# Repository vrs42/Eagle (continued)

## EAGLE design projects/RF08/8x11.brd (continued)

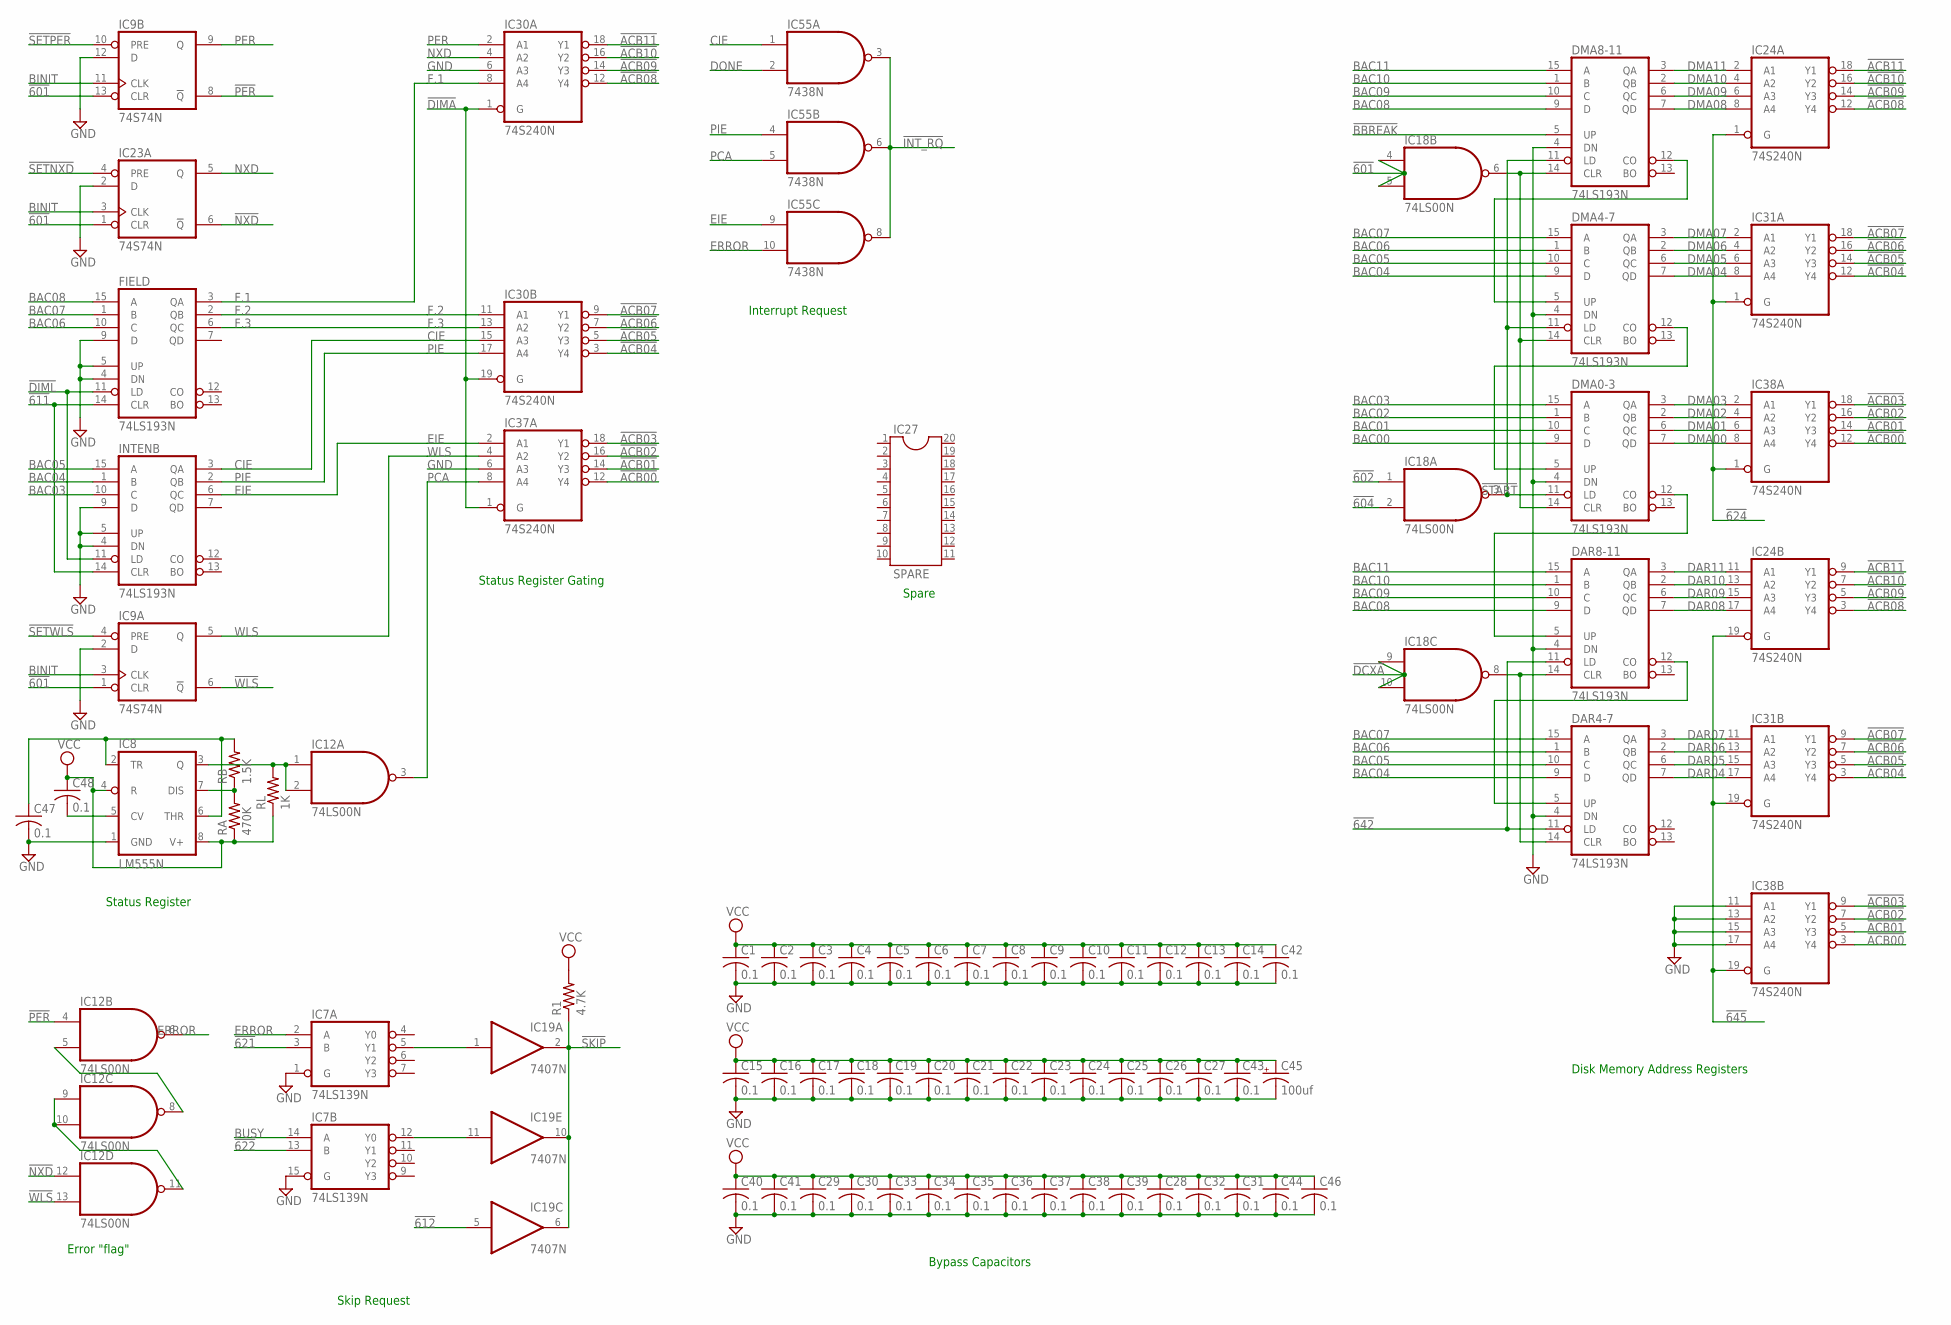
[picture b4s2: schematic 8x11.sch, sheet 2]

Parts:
C1, C2, C3, C4, C5, C6, C7, C8, C9, C10, C11, C12, C13, C14, C15, C16, C17, C18, C19, C20, C21, C22, C23, C24, C25, C26, C27, C28, C29, C30, C31, C32, C33, C34, C35, C36, C37, C38, C39, C40, C41, C42, C43, C44, C46, C47, C48: 0.1; C050-025X075
C45: 100uf; E22-6
DAR4-7, DAR8-11: 74LS193N; DIL16
DMA0-3, DMA4-7, DMA8-11: 74LS193N; DIL16
FIELD: 74LS193N; DIL16
IC7: 74LS139N; DIL16
IC8: LM555N; DIL08
IC9, IC23: 74S74N; DIL14
IC12, IC18: 74LS00N; DIL14
IC19: 7407N; DIL14
IC24, IC30, IC31, IC37, IC38: 74S240N; DIL20
IC27: SPARE; DIL20
IC55: 7438N; DIL14
INTENB: 74LS193N; DIL16
R1: 4.7K; 0207/10
RA: 470K; 0207/10
RB: 1.5K; 0207/10
RL: 1K; 0207/10

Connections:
!601: IC9.1 (CLR), IC9.13 (CLR), IC18.4 (I0), IC18.5 (I1), IC23.1 (CLR); also elsewhere on the board
!602: IC18.1 (I0); also elsewhere on the board
!604: IC18.2 (I1); also elsewhere on the board
!611: FIELD.14 (CLR), INTENB.14 (CLR); also elsewhere on the board
!612: IC19.5 (I); also elsewhere on the board
!621: IC7.3 (B); also elsewhere on the board
!622: IC7.13 (B); also elsewhere on the board
!624: IC24.1 (G), IC31.1 (G), IC38.1 (G); also elsewhere on the board
!642: DAR4-7.11 (LD), DAR8-11.11 (LD); also elsewhere on the board
!645: IC24.19 (G), IC31.19 (G), IC38.19 (G); also elsewhere on the board
!ACB00: IC37.12 (Y4), IC38.3 (Y4), IC38.12 (Y4); also elsewhere on the board
!ACB01: IC37.14 (Y3), IC38.5 (Y3), IC38.14 (Y3); also elsewhere on the board
!ACB02: IC37.16 (Y2), IC38.7 (Y2), IC38.16 (Y2); also elsewhere on the board
!ACB03: IC37.18 (Y1), IC38.9 (Y1), IC38.18 (Y1); also elsewhere on the board
!ACB04: IC30.3 (Y4), IC31.3 (Y4), IC31.12 (Y4); also elsewhere on the board
!ACB05: IC30.5 (Y3), IC31.5 (Y3), IC31.14 (Y3); also elsewhere on the board
!ACB06: IC30.7 (Y2), IC31.7 (Y2), IC31.16 (Y2); also elsewhere on the board
!ACB07: IC30.9 (Y1), IC31.9 (Y1), IC31.18 (Y1); also elsewhere on the board
!ACB08: IC24.3 (Y4), IC24.12 (Y4), IC30.12 (Y4); also elsewhere on the board
!ACB09: IC24.5 (Y3), IC24.14 (Y3), IC30.14 (Y3); also elsewhere on the board
!ACB10: IC24.7 (Y2), IC24.16 (Y2), IC30.16 (Y2); also elsewhere on the board
!ACB11: IC24.9 (Y1), IC24.18 (Y1), IC30.18 (Y1); also elsewhere on the board
!BBREAK: DMA8-11.5 (UP); also elsewhere on the board
!DCXA: IC18.9 (I0), IC18.10 (I1); also elsewhere on the board
!DIMA: IC30.1 (G), IC30.19 (G), IC37.1 (G); also elsewhere on the board
!DIML: FIELD.11 (LD), INTENB.11 (LD); also elsewhere on the board
!INT_RQ: IC55.3 (O), IC55.6 (O), IC55.8 (O); also elsewhere on the board
!NXD: IC12.12 (I0), IC23.6 (!Q)
!PER: IC9.8 (!Q), IC12.4 (I0)
!SETNXD: IC23.4 (PRE); also elsewhere on the board
!SETPER: IC9.10 (PRE); also elsewhere on the board
!SETWLS: IC9.4 (PRE); also elsewhere on the board
!SKIP: IC19.2 (O), IC19.6 (O), IC19.10 (O), R1.1; also elsewhere on the board
!START: DMA0-3.11 (LD), DMA4-7.11 (LD), DMA8-11.11 (LD), IC18.3 (O)
!WLS: IC9.6 (!Q), IC12.13 (I1)
BAC00: DMA0-3.9 (D); also elsewhere on the board
BAC01: DMA0-3.10 (C); also elsewhere on the board
BAC02: DMA0-3.1 (B); also elsewhere on the board
BAC03: DMA0-3.15 (A), INTENB.10 (C); also elsewhere on the board
BAC04: DAR4-7.9 (D), DMA4-7.9 (D), INTENB.1 (B); also elsewhere on the board
BAC05: DAR4-7.10 (C), DMA4-7.10 (C), INTENB.15 (A); also elsewhere on the board
BAC06: DAR4-7.1 (B), DMA4-7.1 (B), FIELD.10 (C); also elsewhere on the board
BAC07: DAR4-7.15 (A), DMA4-7.15 (A), FIELD.1 (B); also elsewhere on the board
BAC08: DAR8-11.9 (D), DMA8-11.9 (D), FIELD.15 (A); also elsewhere on the board
BAC09: DAR8-11.10 (C), DMA8-11.10 (C); also elsewhere on the board
BAC10: DAR8-11.1 (B), DMA8-11.1 (B); also elsewhere on the board
BAC11: DAR8-11.15 (A), DMA8-11.15 (A); also elsewhere on the board
BINIT: IC9.3 (CLK), IC9.11 (CLK), IC23.3 (CLK); also elsewhere on the board
BUSY: IC7.14 (A); also elsewhere on the board
CIE: IC30.15 (A3), IC55.1 (I0), INTENB.3 (QA); also elsewhere on the board
DAR04: DAR4-7.7 (QD), IC31.17 (A4); also elsewhere on the board
DAR05: DAR4-7.6 (QC), IC31.15 (A3); also elsewhere on the board
DAR06: DAR4-7.2 (QB), IC31.13 (A2); also elsewhere on the board
DAR07: DAR4-7.3 (QA), IC31.11 (A1); also elsewhere on the board
DAR08: DAR8-11.7 (QD), IC24.17 (A4); also elsewhere on the board
DAR09: DAR8-11.6 (QC), IC24.15 (A3); also elsewhere on the board
DAR10: DAR8-11.2 (QB), IC24.13 (A2); also elsewhere on the board
DAR11: DAR8-11.3 (QA), IC24.11 (A1); also elsewhere on the board
DMA00: DMA0-3.7 (QD), IC38.8 (A4); also elsewhere on the board
DMA01: DMA0-3.6 (QC), IC38.6 (A3); also elsewhere on the board
DMA02: DMA0-3.2 (QB), IC38.4 (A2); also elsewhere on the board
DMA03: DMA0-3.3 (QA), IC38.2 (A1); also elsewhere on the board
DMA04: DMA4-7.7 (QD), IC31.8 (A4); also elsewhere on the board
DMA05: DMA4-7.6 (QC), IC31.6 (A3); also elsewhere on the board
DMA06: DMA4-7.2 (QB), IC31.4 (A2); also elsewhere on the board
DMA07: DMA4-7.3 (QA), IC31.2 (A1); also elsewhere on the board
DMA08: DMA8-11.7 (QD), IC24.8 (A4); also elsewhere on the board
DMA09: DMA8-11.6 (QC), IC24.6 (A3); also elsewhere on the board
DMA10: DMA8-11.2 (QB), IC24.4 (A2); also elsewhere on the board
DMA11: DMA8-11.3 (QA), IC24.2 (A1); also elsewhere on the board
DONE: IC55.2 (I1); also elsewhere on the board
EIE: IC37.2 (A1), IC55.9 (I0), INTENB.6 (QC); also elsewhere on the board
ERROR: IC7.2 (A), IC12.6 (O), IC55.10 (I1)
F.1: FIELD.3 (QA), IC30.8 (A4); also elsewhere on the board
F.2: FIELD.2 (QB), IC30.11 (A1); also elsewhere on the board
F.3: FIELD.6 (QC), IC30.13 (A2); also elsewhere on the board
GND: C1.2, C2.2, C3.2, C4.2, C5.2, C6.2, C7.2, C8.2, C9.2, C10.2, C11.2, C12.2, C13.2, C14.2, C15.2, C16.2, C17.2, C18.2, C19.2, C20.2, C21.2, C22.2, C23.2, C24.2, C25.2, C26.2, C27.2, C28.2, C29.2, C30.2, C31.2, C32.2, C33.2, C34.2, C35.2, C36.2, C37.2, C38.2, C39.2, C40.2, C41.2, C42.2, C43.2, C44.2, C45.-, C46.2, C47.2, DAR4-7.4 (DN), DAR4-7.8 (GND), DAR8-11.4 (DN), DAR8-11.8 (GND), DMA0-3.4 (DN), DMA0-3.8 (GND), DMA4-7.4 (DN), DMA4-7.8 (GND), DMA8-11.4 (DN), DMA8-11.8 (GND), FIELD.4 (DN), FIELD.5 (UP), FIELD.8 (GND), FIELD.9 (D), IC7.1 (G), IC7.8 (GND), IC7.15 (G), IC8.1 (GND), IC9.2 (D), IC9.7 (GND), IC9.12 (D), IC12.7 (GND), IC18.7 (GND), IC19.7 (GND), IC23.2 (D), IC23.7 (GND), IC24.10 (GND), IC30.6 (A3), IC30.10 (GND), IC31.10 (GND), IC37.6 (A3), IC37.10 (GND), IC38.10 (GND), IC38.11 (A1), IC38.13 (A2), IC38.15 (A3), IC38.17 (A4), IC55.7 (GND), INTENB.4 (DN), INTENB.5 (UP), INTENB.8 (GND), INTENB.9 (D); also elsewhere on the board
unnamed: DMA0-3.5 (UP), DMA4-7.12 (CO)
unnamed: DAR4-7.14 (CLR), DAR8-11.14 (CLR), IC18.8 (O)
unnamed: DMA4-7.5 (UP), DMA8-11.12 (CO)
unnamed: DAR8-11.5 (UP), DMA0-3.12 (CO)
unnamed: DMA0-3.14 (CLR), DMA4-7.14 (CLR), DMA8-11.14 (CLR), IC18.6 (O)
unnamed: DAR4-7.5 (UP), DAR8-11.12 (CO)
unnamed: IC7.5 (Y1), IC19.1 (I)
unnamed: IC8.7 (DIS), RA.2, RB.1
unnamed: IC8.3 (Q), IC12.1 (I0), IC12.2 (I1), RL.2
unnamed: C47.1, IC8.2 (TR), IC8.6 (THR), RB.2
unnamed: IC7.12 (Y0), IC19.11 (I)
unnamed: C48.2, IC8.5 (CV)
unnamed: IC12.9 (I0), IC12.10 (I1), IC12.11 (O)
unnamed: IC12.5 (I1), IC12.8 (O)
NXD: IC23.5 (Q), IC30.4 (A2); also elsewhere on the board
PCA: IC12.3 (O), IC37.8 (A4), IC55.5 (I1)
PER: IC9.9 (Q), IC30.2 (A1); also elsewhere on the board
PIE: IC30.17 (A4), IC55.4 (I0), INTENB.2 (QB); also elsewhere on the board
VCC: C1.1, C2.1, C3.1, C4.1, C5.1, C6.1, C7.1, C8.1, C9.1, C10.1, C11.1, C12.1, C13.1, C14.1, C15.1, C16.1, C17.1, C18.1, C19.1, C20.1, C21.1, C22.1, C23.1, C24.1, C25.1, C26.1, C27.1, C28.1, C29.1, C30.1, C31.1, C32.1, C33.1, C34.1, C35.1, C36.1, C37.1, C38.1, C39.1, C40.1, C41.1, C42.1, C43.1, C44.1, C45.+, C46.1, C48.1, DAR4-7.16 (VCC), DAR8-11.16 (VCC), DMA0-3.16 (VCC), DMA4-7.16 (VCC), DMA8-11.16 (VCC), FIELD.16 (VCC), IC7.16 (VCC), IC8.4 (R), IC8.8 (V+), IC9.14 (VCC), IC12.14 (VCC), IC18.14 (VCC), IC19.14 (VCC), IC23.14 (VCC), IC24.20 (VCC), IC30.20 (VCC), IC31.20 (VCC), IC37.20 (VCC), IC38.20 (VCC), IC55.14 (VCC), INTENB.16 (VCC), R1.2, RA.1, RL.1; also elsewhere on the board
WLS: IC9.5 (Q), IC37.4 (A2); also elsewhere on the board

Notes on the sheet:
Disk Memory Address Registers
Status Register
Status Register Gating
Interrupt Request
Error "flag"
Skip Request
Spare
Bypass Capacitors

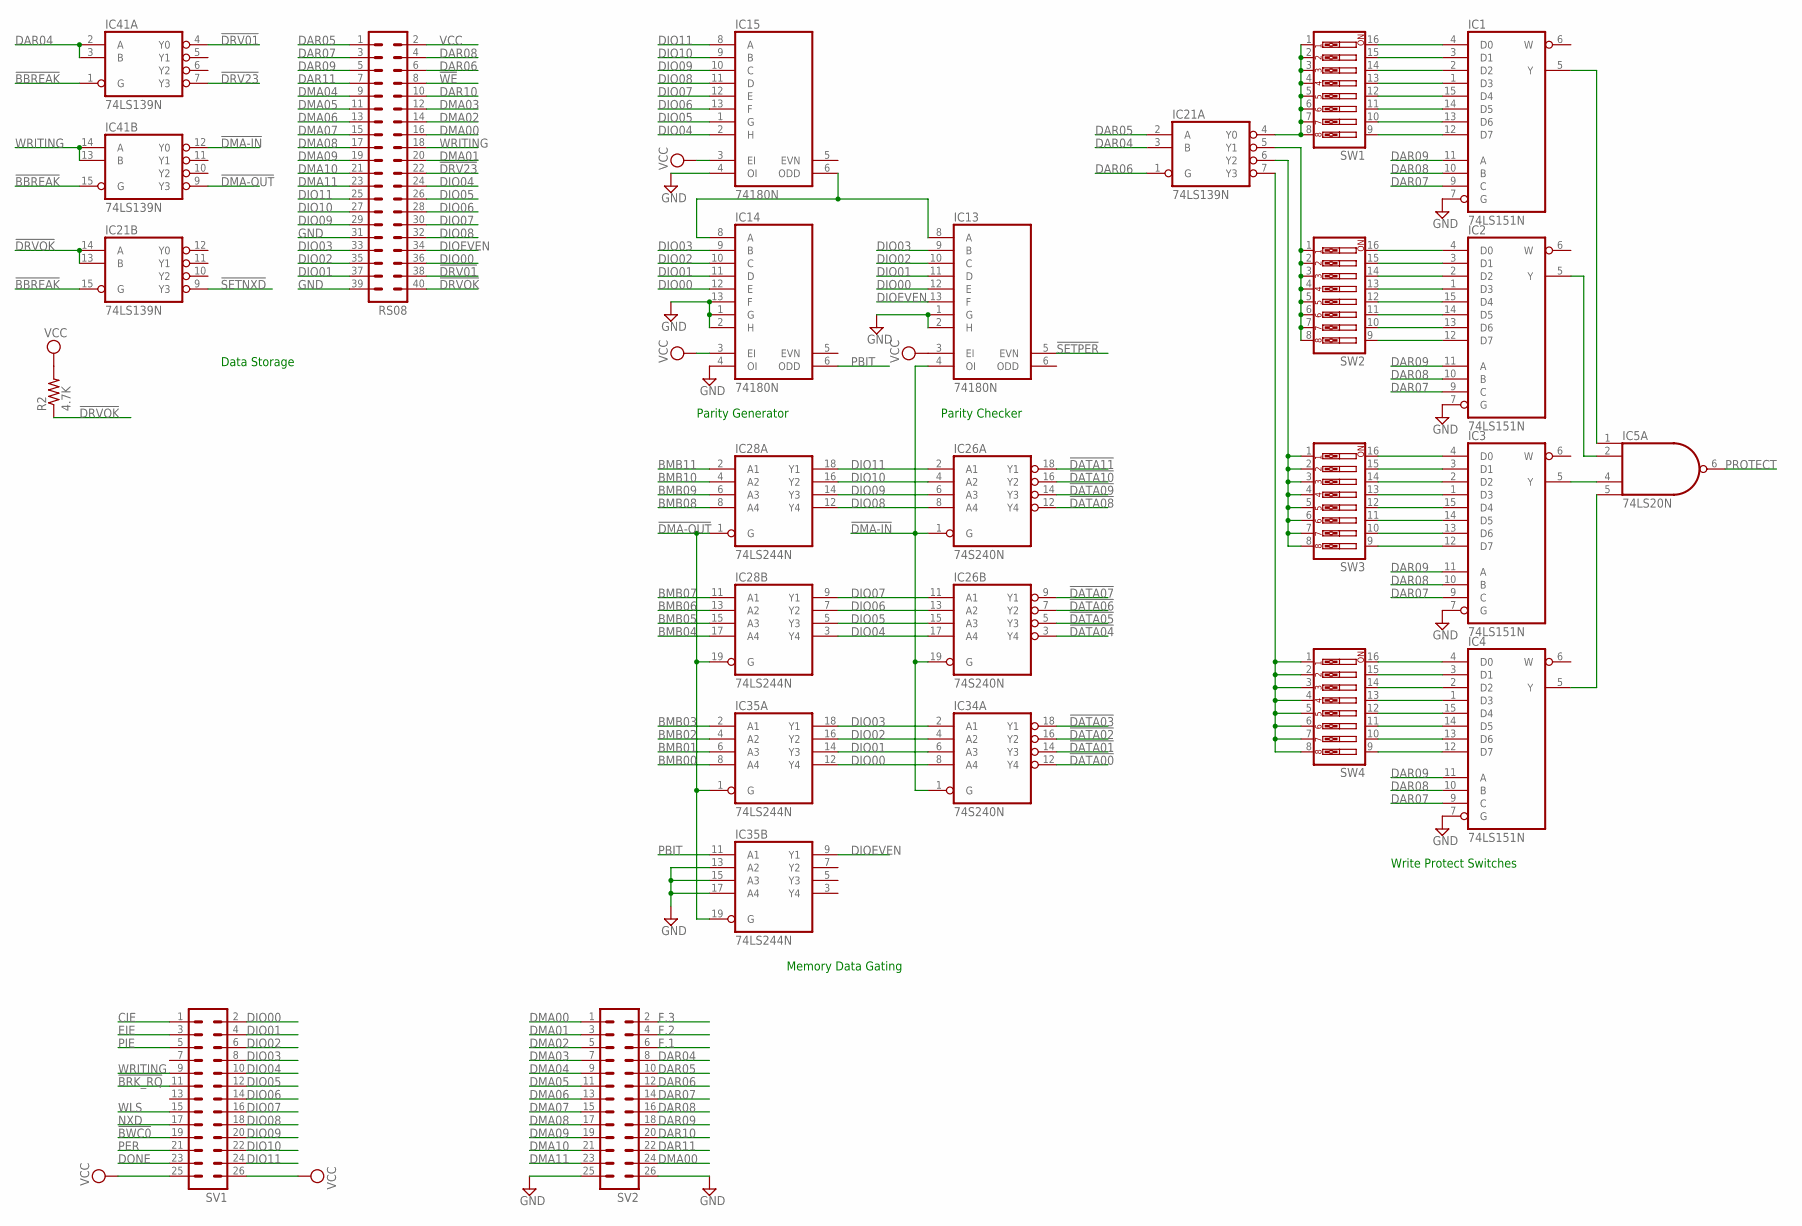
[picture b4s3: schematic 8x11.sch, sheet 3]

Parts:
IC1, IC2, IC3, IC4: 74LS151N; DIL16
IC5: 74LS20N; DIL14
IC13, IC14, IC15: 74180N; DIL14
IC21, IC41: 74LS139N; DIL16
IC26, IC34: 74S240N; DIL20
IC28, IC35: 74LS244N; DIL20
R2: 4.7K; 0207/10
RS08: MA20-2
SV1, SV2: MA13-2
SW1, SW2, SW3, SW4: SW_DIP-8; EDG-08

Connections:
!BBREAK: IC21.15 (G), IC41.1 (G), IC41.15 (G); also elsewhere on the board
!BRK_RQ: SV1.11; also elsewhere on the board
!BWC0: SV1.19; also elsewhere on the board
!DATA00: IC34.12 (Y4); also elsewhere on the board
!DATA01: IC34.14 (Y3); also elsewhere on the board
!DATA02: IC34.16 (Y2); also elsewhere on the board
!DATA03: IC34.18 (Y1); also elsewhere on the board
!DATA04: IC26.3 (Y4); also elsewhere on the board
!DATA05: IC26.5 (Y3); also elsewhere on the board
!DATA06: IC26.7 (Y2); also elsewhere on the board
!DATA07: IC26.9 (Y1); also elsewhere on the board
!DATA08: IC26.12 (Y4); also elsewhere on the board
!DATA09: IC26.14 (Y3); also elsewhere on the board
!DATA10: IC26.16 (Y2); also elsewhere on the board
!DATA11: IC26.18 (Y1); also elsewhere on the board
!DMA-IN: IC13.4 (OI), IC26.1 (G), IC26.19 (G), IC34.1 (G), IC41.12 (Y0)
!DMA-OUT: IC28.1 (G), IC28.19 (G), IC35.1 (G), IC35.19 (G), IC41.9 (Y3)
!DRV01: IC41.4 (Y0), RS08.38; also elsewhere on the board
!DRV23: IC41.7 (Y3), RS08.22; also elsewhere on the board
!DRVOK: IC21.13 (B), IC21.14 (A), R2.1, RS08.40; also elsewhere on the board
!SETNXD: IC21.9 (Y3); also elsewhere on the board
!SETPER: IC13.5 (EVN); also elsewhere on the board
!WE: RS08.8; also elsewhere on the board
BMB00: IC35.8 (A4); also elsewhere on the board
BMB01: IC35.6 (A3); also elsewhere on the board
BMB02: IC35.4 (A2); also elsewhere on the board
BMB03: IC35.2 (A1); also elsewhere on the board
BMB04: IC28.17 (A4); also elsewhere on the board
BMB05: IC28.15 (A3); also elsewhere on the board
BMB06: IC28.13 (A2); also elsewhere on the board
BMB07: IC28.11 (A1); also elsewhere on the board
BMB08: IC28.8 (A4); also elsewhere on the board
BMB09: IC28.6 (A3); also elsewhere on the board
BMB10: IC28.4 (A2); also elsewhere on the board
BMB11: IC28.2 (A1); also elsewhere on the board
CIE: SV1.1; also elsewhere on the board
DAR04: IC21.3 (B), IC41.2 (A), IC41.3 (B), SV2.8; also elsewhere on the board
DAR05: IC21.2 (A), RS08.1, SV2.10; also elsewhere on the board
DAR06: IC21.1 (G), RS08.6, SV2.12; also elsewhere on the board
DAR07: IC1.9 (C), IC2.9 (C), IC3.9 (C), IC4.9 (C), RS08.3, SV2.14; also elsewhere on the board
DAR08: IC1.10 (B), IC2.10 (B), IC3.10 (B), IC4.10 (B), RS08.4, SV2.16; also elsewhere on the board
DAR09: IC1.11 (A), IC2.11 (A), IC3.11 (A), IC4.11 (A), RS08.5, SV2.18; also elsewhere on the board
DAR10: RS08.10, SV2.20; also elsewhere on the board
DAR11: RS08.7, SV2.22; also elsewhere on the board
DIO00: IC13.12 (E), IC14.12 (E), IC34.8 (A4), IC35.12 (Y4), RS08.36, SV1.2; also elsewhere on the board
DIO01: IC13.11 (D), IC14.11 (D), IC34.6 (A3), IC35.14 (Y3), RS08.37, SV1.4; also elsewhere on the board
DIO02: IC13.10 (C), IC14.10 (C), IC34.4 (A2), IC35.16 (Y2), RS08.35, SV1.6; also elsewhere on the board
DIO03: IC13.9 (B), IC14.9 (B), IC34.2 (A1), IC35.18 (Y1), RS08.33, SV1.8; also elsewhere on the board
DIO04: IC15.2 (H), IC26.17 (A4), IC28.3 (Y4), RS08.24, SV1.10; also elsewhere on the board
DIO05: IC15.1 (G), IC26.15 (A3), IC28.5 (Y3), RS08.26, SV1.12; also elsewhere on the board
DIO06: IC15.13 (F), IC26.13 (A2), IC28.7 (Y2), RS08.28, SV1.14; also elsewhere on the board
DIO07: IC15.12 (E), IC26.11 (A1), IC28.9 (Y1), RS08.30, SV1.16; also elsewhere on the board
DIO08: IC15.11 (D), IC26.8 (A4), IC28.12 (Y4), RS08.32, SV1.18; also elsewhere on the board
DIO09: IC15.10 (C), IC26.6 (A3), IC28.14 (Y3), RS08.29, SV1.20; also elsewhere on the board
DIO10: IC15.9 (B), IC26.4 (A2), IC28.16 (Y2), RS08.27, SV1.22; also elsewhere on the board
DIO11: IC15.8 (A), IC26.2 (A1), IC28.18 (Y1), RS08.25, SV1.24; also elsewhere on the board
DIOEVEN: IC13.13 (F), IC35.9 (Y1), RS08.34; also elsewhere on the board
DMA00: RS08.16, SV2.1, SV2.24; also elsewhere on the board
DMA01: RS08.20, SV2.3; also elsewhere on the board
DMA02: RS08.14, SV2.5; also elsewhere on the board
DMA03: RS08.12, SV2.7; also elsewhere on the board
DMA04: RS08.9, SV2.9; also elsewhere on the board
DMA05: RS08.11, SV2.11; also elsewhere on the board
DMA06: RS08.13, SV2.13; also elsewhere on the board
DMA07: RS08.15, SV2.15; also elsewhere on the board
DMA08: RS08.17, SV2.17; also elsewhere on the board
DMA09: RS08.19, SV2.19; also elsewhere on the board
DMA10: RS08.21, SV2.21; also elsewhere on the board
DMA11: RS08.23, SV2.23; also elsewhere on the board
DONE: SV1.23; also elsewhere on the board
EIE: SV1.3; also elsewhere on the board
F.1: SV2.6; also elsewhere on the board
F.2: SV2.4; also elsewhere on the board
F.3: SV2.2; also elsewhere on the board
GND: IC1.7 (G), IC1.8 (GND), IC2.7 (G), IC2.8 (GND), IC3.7 (G), IC3.8 (GND), IC4.7 (G), IC4.8 (GND), IC5.7 (GND), IC13.1 (G), IC13.2 (H), IC13.7 (GND), IC14.1 (G), IC14.2 (H), IC14.4 (OI), IC14.7 (GND), IC14.13 (F), IC15.4 (OI), IC15.7 (GND), IC21.8 (GND), IC26.10 (GND), IC28.10 (GND), IC34.10 (GND), IC35.10 (GND), IC35.13 (A2), IC35.15 (A3), IC35.17 (A4), IC41.8 (GND), RS08.31, RS08.39, SV2.25, SV2.26; also elsewhere on the board
unnamed: IC21.4 (Y0), SW1.1, SW1.2, SW1.3, SW1.4, SW1.5, SW1.6, SW1.7, SW1.8
unnamed: IC13.8 (A), IC14.8 (A), IC15.6 (ODD)
unnamed: IC2.5 (Y), IC5.2 (I1)
unnamed: IC21.5 (Y1), SW2.1, SW2.2, SW2.3, SW2.4, SW2.5, SW2.6, SW2.7, SW2.8
unnamed: IC21.6 (Y2), SW3.1, SW3.2, SW3.3, SW3.4, SW3.5, SW3.6, SW3.7, SW3.8
unnamed: IC21.7 (Y3), SW4.1, SW4.2, SW4.3, SW4.4, SW4.5, SW4.6, SW4.7, SW4.8
unnamed: IC3.5 (Y), IC5.4 (I2)
unnamed: IC1.5 (Y), IC5.1 (I0)
unnamed: IC4.5 (Y), IC5.5 (I3)
unnamed: IC1.4 (D0), SW1.16
unnamed: IC1.3 (D1), SW1.15
unnamed: IC1.2 (D2), SW1.14
unnamed: IC1.1 (D3), SW1.13
unnamed: IC1.14 (D5), SW1.11
unnamed: IC1.13 (D6), SW1.10
unnamed: IC1.12 (D7), SW1.9
unnamed: IC1.15 (D4), SW1.12
unnamed: IC2.4 (D0), SW2.16
unnamed: IC2.3 (D1), SW2.15
unnamed: IC2.2 (D2), SW2.14
unnamed: IC2.1 (D3), SW2.13
unnamed: IC2.14 (D5), SW2.11
unnamed: IC2.13 (D6), SW2.10
unnamed: IC2.12 (D7), SW2.9
unnamed: IC3.4 (D0), SW3.16
unnamed: IC3.3 (D1), SW3.15
unnamed: IC3.2 (D2), SW3.14
unnamed: IC3.1 (D3), SW3.13
unnamed: IC3.14 (D5), SW3.11
unnamed: IC3.13 (D6), SW3.10
unnamed: IC3.12 (D7), SW3.9
unnamed: IC4.4 (D0), SW4.16
unnamed: IC4.3 (D1), SW4.15
unnamed: IC4.2 (D2), SW4.14
unnamed: IC4.1 (D3), SW4.13
unnamed: IC4.14 (D5), SW4.11
unnamed: IC4.13 (D6), SW4.10
unnamed: IC4.12 (D7), SW4.9
unnamed: IC4.15 (D4), SW4.12
unnamed: IC3.15 (D4), SW3.12
unnamed: IC2.15 (D4), SW2.12
NXD: SV1.17; also elsewhere on the board
PBIT: IC14.6 (ODD), IC35.11 (A1)
PER: SV1.21; also elsewhere on the board
PIE: SV1.5; also elsewhere on the board
PROTECT: IC5.6 (O); also elsewhere on the board
VCC: IC1.16 (VCC), IC2.16 (VCC), IC3.16 (VCC), IC4.16 (VCC), IC5.14 (VCC), IC13.3 (EI), IC13.14 (VCC), IC14.3 (EI), IC14.14 (VCC), IC15.3 (EI), IC15.14 (VCC), IC21.16 (VCC), IC26.20 (VCC), IC28.20 (VCC), IC34.20 (VCC), IC35.20 (VCC), IC41.16 (VCC), R2.2, RS08.2, SV1.25, SV1.26; also elsewhere on the board
WLS: SV1.15; also elsewhere on the board
WRITING: IC41.13 (B), IC41.14 (A), RS08.18, SV1.9; also elsewhere on the board

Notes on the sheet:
Parity Generator
Parity Checker
Memory Data Gating
Write Protect Switches
Data Storage

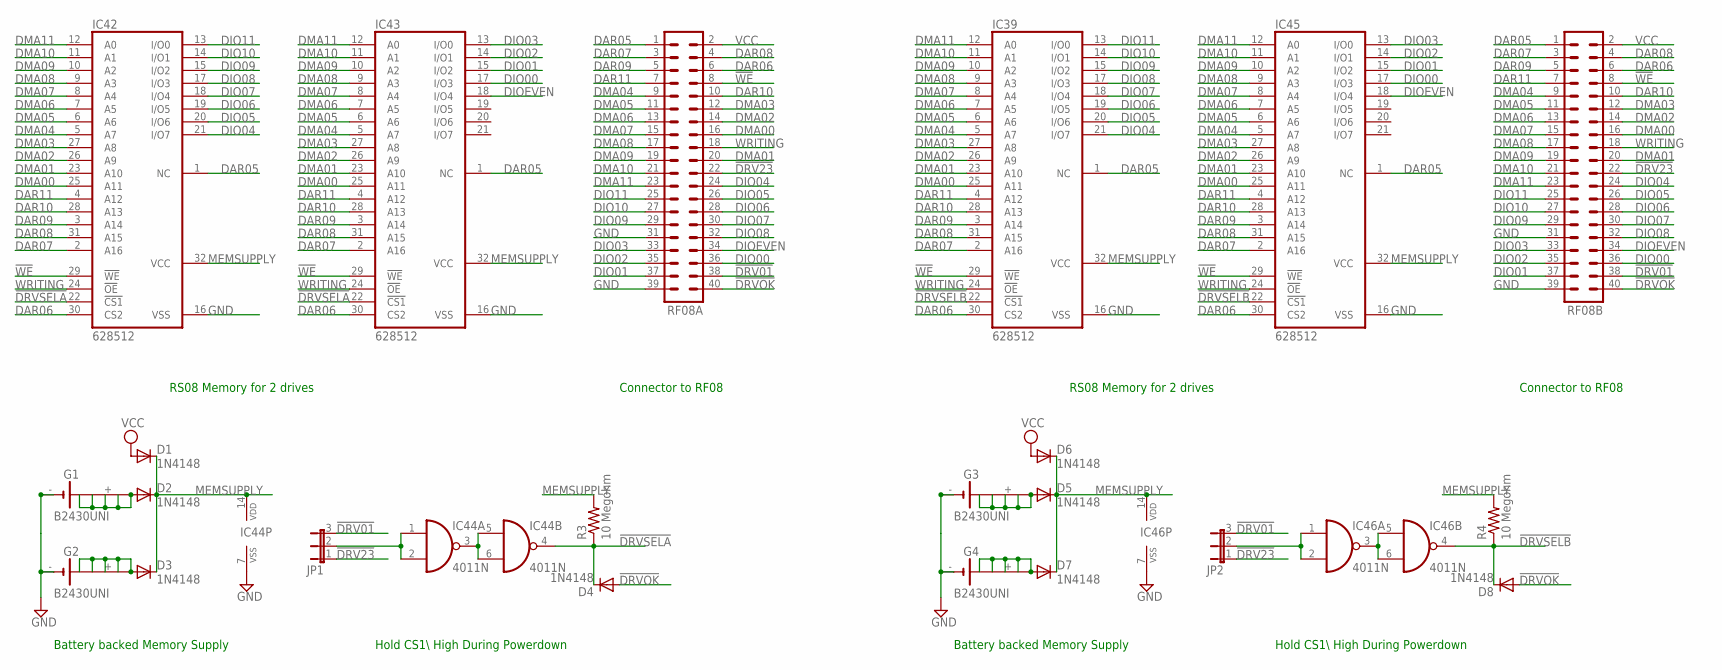
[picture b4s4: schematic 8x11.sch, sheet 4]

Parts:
D1, D2, D3, D4, D5, D6, D7, D8: 1N4148; DO35-10
G1, G2, G3, G4: B2430UNI
IC39, IC42, IC43, IC45: 628512; DIL32
IC44, IC46: 4011N; DIL14
JP1, JP2: JP2E; JP2
R3, R4: 10 Megohm; 0207/10
RF08A, RF08B: MA20-2

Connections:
!DRV01: JP1.3, JP2.3, RF08A.38, RF08B.38; also elsewhere on the board
!DRV23: JP1.1, JP2.1, RF08A.22, RF08B.22; also elsewhere on the board
!DRVOK: D4.A, D8.A, RF08A.40, RF08B.40; also elsewhere on the board
!DRVSELA: D4.C, IC42.22 (!CS1), IC43.22 (!CS1), IC44.4 (O), R3.1
!DRVSELB: D8.C, IC39.22 (!CS1), IC45.22 (!CS1), IC46.4 (O), R4.1
!WE: IC39.29 (!WE), IC42.29 (!WE), IC43.29 (!WE), IC45.29 (!WE), RF08A.8, RF08B.8; also elsewhere on the board
DAR05: IC39.1 (NC), IC42.1 (NC), IC43.1 (NC), IC45.1 (NC), RF08A.1, RF08B.1; also elsewhere on the board
DAR06: IC39.30 (CS2), IC42.30 (CS2), IC43.30 (CS2), IC45.30 (CS2), RF08A.6, RF08B.6; also elsewhere on the board
DAR07: IC39.2 (A16), IC42.2 (A16), IC43.2 (A16), IC45.2 (A16), RF08A.3, RF08B.3; also elsewhere on the board
DAR08: IC39.31 (A15), IC42.31 (A15), IC43.31 (A15), IC45.31 (A15), RF08A.4, RF08B.4; also elsewhere on the board
DAR09: IC39.3 (A14), IC42.3 (A14), IC43.3 (A14), IC45.3 (A14), RF08A.5, RF08B.5; also elsewhere on the board
DAR10: IC39.28 (A13), IC42.28 (A13), IC43.28 (A13), IC45.28 (A13), RF08A.10, RF08B.10; also elsewhere on the board
DAR11: IC39.4 (A12), IC42.4 (A12), IC43.4 (A12), IC45.4 (A12), RF08A.7, RF08B.7; also elsewhere on the board
DIO00: IC43.17 (I/O3), IC45.17 (I/O3), RF08A.36, RF08B.36; also elsewhere on the board
DIO01: IC43.15 (I/O2), IC45.15 (I/O2), RF08A.37, RF08B.37; also elsewhere on the board
DIO02: IC43.14 (I/O1), IC45.14 (I/O1), RF08A.35, RF08B.35; also elsewhere on the board
DIO03: IC43.13 (I/O0), IC45.13 (I/O0), RF08A.33, RF08B.33; also elsewhere on the board
DIO04: IC39.21 (I/O7), IC42.21 (I/O7), RF08A.24, RF08B.24; also elsewhere on the board
DIO05: IC39.20 (I/O6), IC42.20 (I/O6), RF08A.26, RF08B.26; also elsewhere on the board
DIO06: IC39.19 (I/O5), IC42.19 (I/O5), RF08A.28, RF08B.28; also elsewhere on the board
DIO07: IC39.18 (I/O4), IC42.18 (I/O4), RF08A.30, RF08B.30; also elsewhere on the board
DIO08: IC39.17 (I/O3), IC42.17 (I/O3), RF08A.32, RF08B.32; also elsewhere on the board
DIO09: IC39.15 (I/O2), IC42.15 (I/O2), RF08A.29, RF08B.29; also elsewhere on the board
DIO10: IC39.14 (I/O1), IC42.14 (I/O1), RF08A.27, RF08B.27; also elsewhere on the board
DIO11: IC39.13 (I/O0), IC42.13 (I/O0), RF08A.25, RF08B.25; also elsewhere on the board
DIOEVEN: IC43.18 (I/O4), IC45.18 (I/O4), RF08A.34, RF08B.34; also elsewhere on the board
DMA00: IC39.25 (A11), IC42.25 (A11), IC43.25 (A11), IC45.25 (A11), RF08A.16, RF08B.16; also elsewhere on the board
DMA01: IC39.23 (A10), IC42.23 (A10), IC43.23 (A10), IC45.23 (A10), RF08A.20, RF08B.20; also elsewhere on the board
DMA02: IC39.26 (A9), IC42.26 (A9), IC43.26 (A9), IC45.26 (A9), RF08A.14, RF08B.14; also elsewhere on the board
DMA03: IC39.27 (A8), IC42.27 (A8), IC43.27 (A8), IC45.27 (A8), RF08A.12, RF08B.12; also elsewhere on the board
DMA04: IC39.5 (A7), IC42.5 (A7), IC43.5 (A7), IC45.5 (A7), RF08A.9, RF08B.9; also elsewhere on the board
DMA05: IC39.6 (A6), IC42.6 (A6), IC43.6 (A6), IC45.6 (A6), RF08A.11, RF08B.11; also elsewhere on the board
DMA06: IC39.7 (A5), IC42.7 (A5), IC43.7 (A5), IC45.7 (A5), RF08A.13, RF08B.13; also elsewhere on the board
DMA07: IC39.8 (A4), IC42.8 (A4), IC43.8 (A4), IC45.8 (A4), RF08A.15, RF08B.15; also elsewhere on the board
DMA08: IC39.9 (A3), IC42.9 (A3), IC43.9 (A3), IC45.9 (A3), RF08A.17, RF08B.17; also elsewhere on the board
DMA09: IC39.10 (A2), IC42.10 (A2), IC43.10 (A2), IC45.10 (A2), RF08A.19, RF08B.19; also elsewhere on the board
DMA10: IC39.11 (A1), IC42.11 (A1), IC43.11 (A1), IC45.11 (A1), RF08A.21, RF08B.21; also elsewhere on the board
DMA11: IC39.12 (A0), IC42.12 (A0), IC43.12 (A0), IC45.12 (A0), RF08A.23, RF08B.23; also elsewhere on the board
GND: G1.-, G1.-@1 (-), G2.-, G2.-@1 (-), G3.-, G3.-@1 (-), G4.-, G4.-@1 (-), IC39.16 (VSS), IC42.16 (VSS), IC43.16 (VSS), IC44.7 (VSS), IC45.16 (VSS), IC46.7 (VSS), RF08A.31, RF08A.39, RF08B.31, RF08B.39; also elsewhere on the board
MEMSUPPLY: D1.C, D2.C, D3.C, D5.C, D6.C, D7.C, IC39.32 (VCC), IC42.32 (VCC), IC43.32 (VCC), IC44.14 (VDD), IC45.32 (VCC), IC46.14 (VDD), R3.2, R4.2
unnamed: IC44.3 (O), IC44.5 (I0), IC44.6 (I1)
unnamed: IC44.1 (I0), IC44.2 (I1), JP1.2
unnamed: D7.A, G4.+, G4.+@1 (+), G4.+@2 (+), G4.+@3 (+), G4.+@4 (+)
unnamed: IC46.3 (O), IC46.5 (I0), IC46.6 (I1)
unnamed: IC46.1 (I0), IC46.2 (I1), JP2.2
unnamed: D5.A, G3.+, G3.+@1 (+), G3.+@2 (+), G3.+@3 (+), G3.+@4 (+)
unnamed: D3.A, G2.+, G2.+@1 (+), G2.+@2 (+), G2.+@3 (+), G2.+@4 (+)
unnamed: D2.A, G1.+, G1.+@1 (+), G1.+@2 (+), G1.+@3 (+), G1.+@4 (+)
VCC: D1.A, D6.A, RF08A.2, RF08B.2; also elsewhere on the board
WRITING: IC39.24 (!OE), IC42.24 (!OE), IC43.24 (!OE), IC45.24 (!OE), RF08A.18, RF08B.18; also elsewhere on the board

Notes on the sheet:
Hold CS1\\ High During Powerdown
Battery backed Memory Supply
RS08 Memory for 2 drives
Connector to RF08
